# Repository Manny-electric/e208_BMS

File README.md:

# e208_BMS

This PCB can be used as a BMS for battery modules using the MAX17823BG BMS chip.
Modules that use this chip can be found in PSA cars like:
* Corsa-E
* Peugoet e-208 

This designe is based on work by bexander on the Openinverter Forum
https://openinverter.org/forum/viewtopic.php?t=1179&sid=5e96214b2f58e9805228647a1629a734

The PCB can be mounted in a Cinch encluosere 
* 581-01-30-065 main enclosure
* 581-01-18-038 Front / connector
* 581-01-18-023 Plug
* 425-00-00-872 pins

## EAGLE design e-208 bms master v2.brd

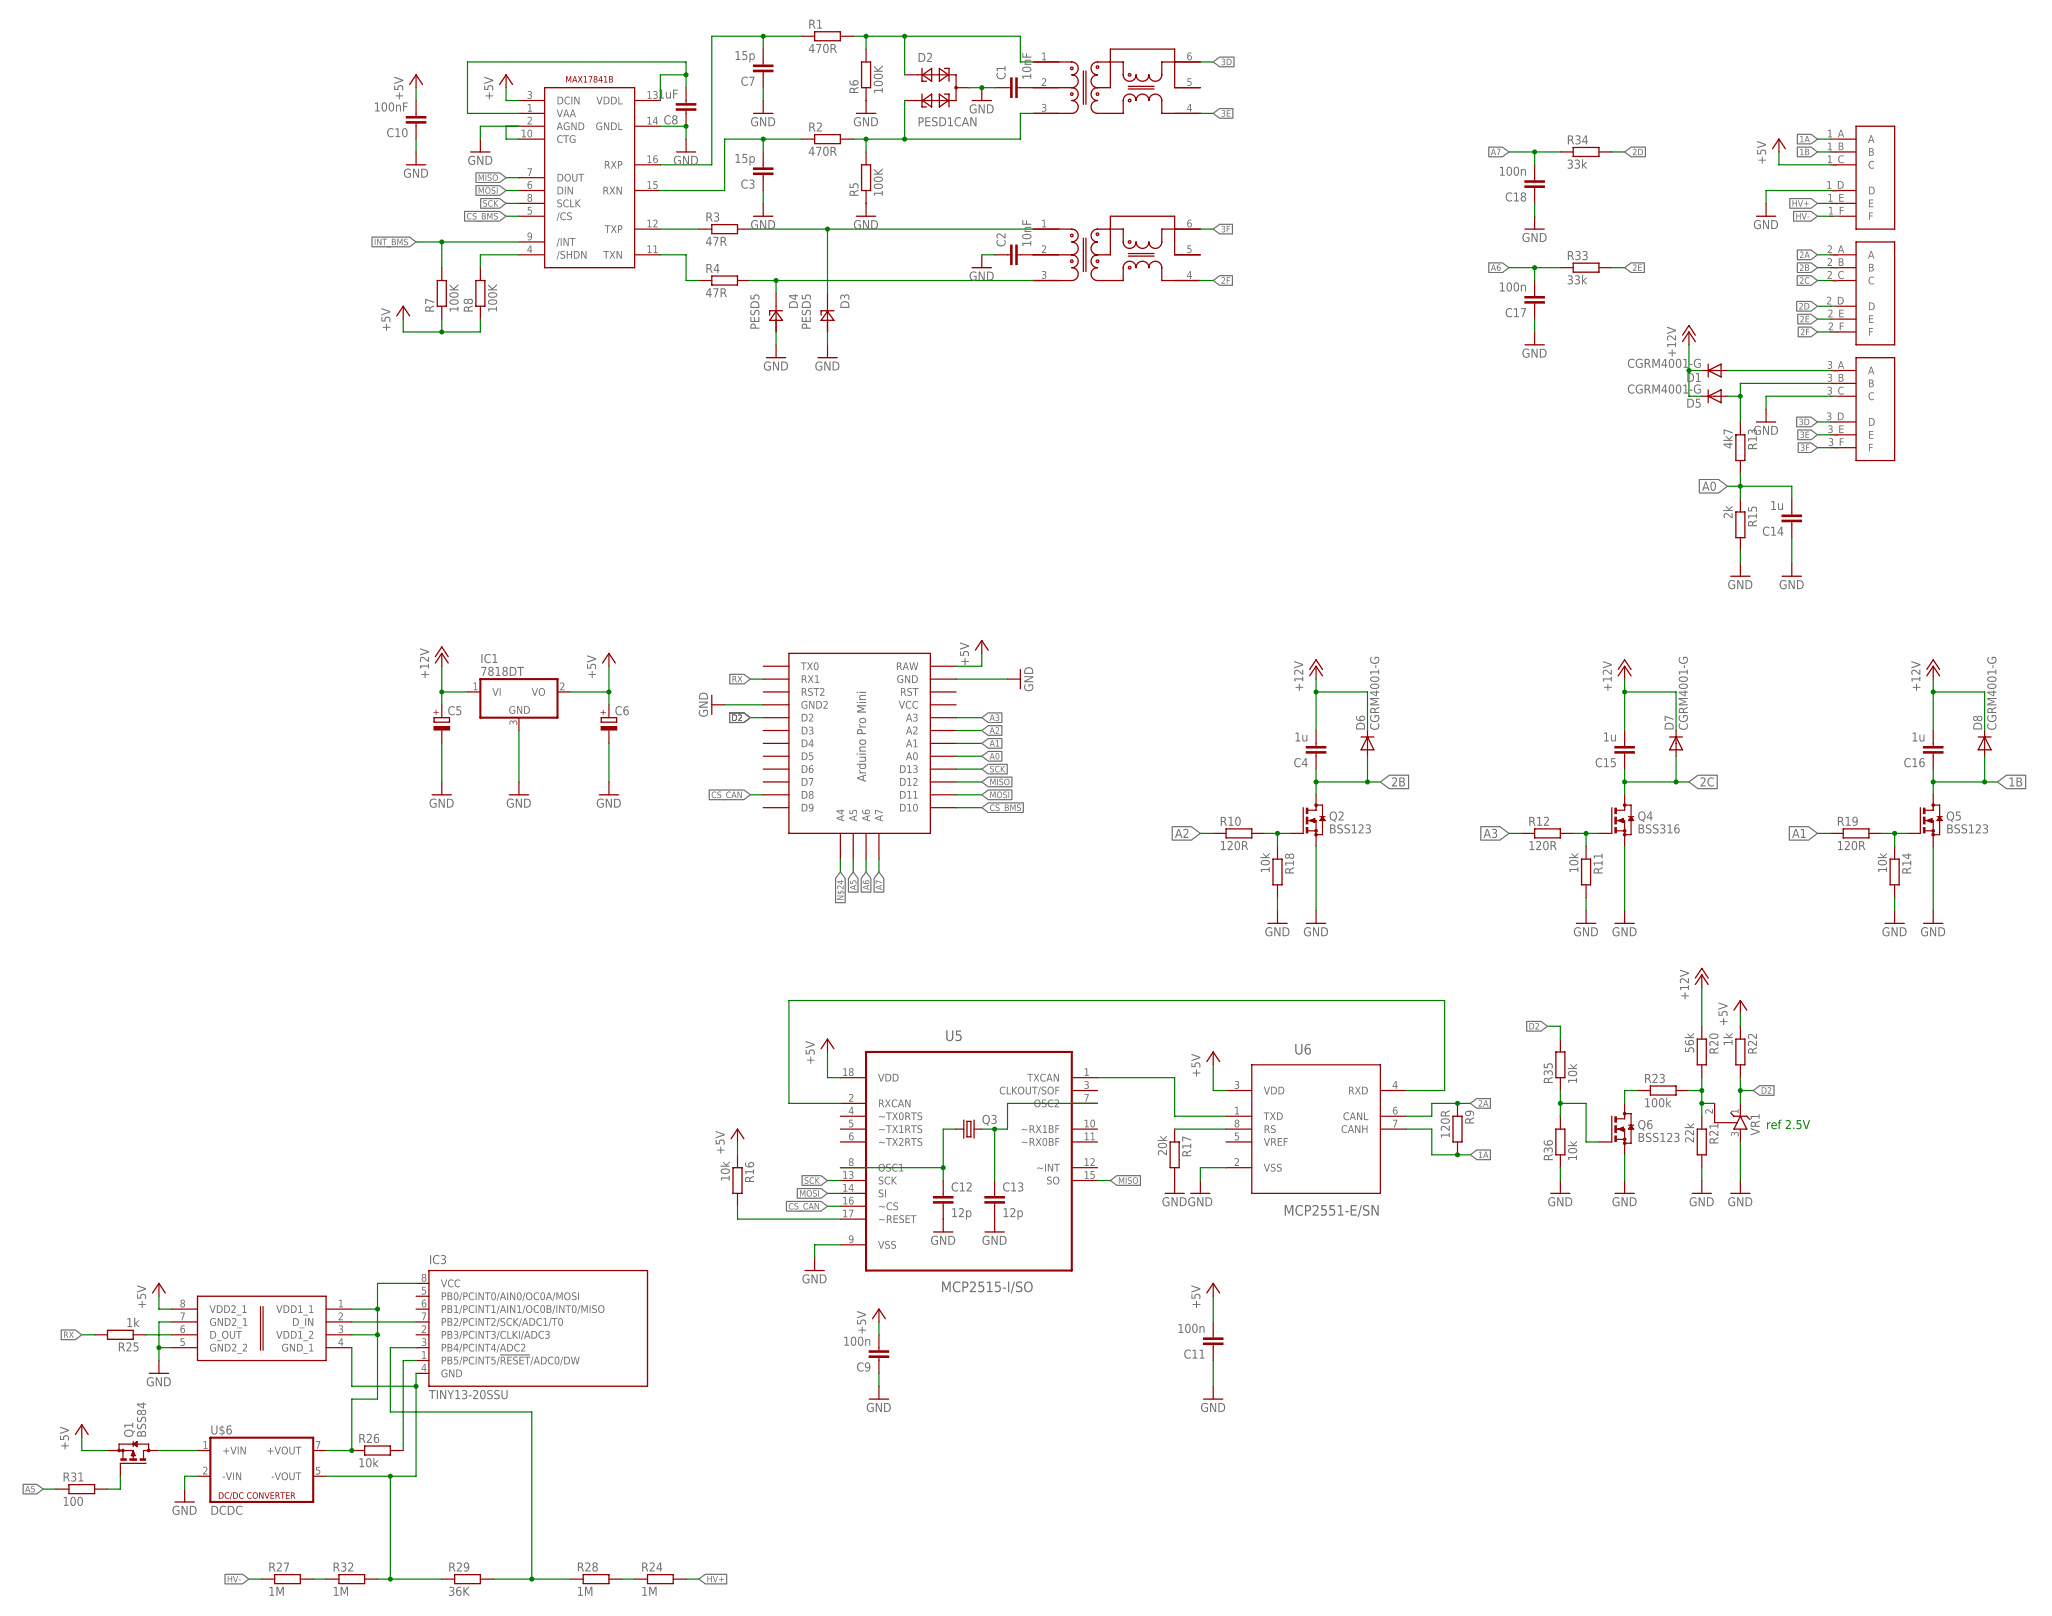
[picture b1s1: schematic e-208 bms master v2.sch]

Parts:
C1, C2: 10nF; C0805
C3, C7: 15p; C0805
C4, C14, C15, C16: 1u; C0805
C5, C6: CPOL-EU153CLV-1010; 153CLV-1010
C8: 1uF; C0805
C9, C11, C17, C18: 100n; C0805
C10: 100nF; C0805
C12, C13: 12p; C0603
D1, D5, D6, D7, D8: CGRM4001-G; SOD-123_MINI-SMA
D2: PESD1CAN; SOT23
D3, D4: PESD5; SOD323
IC1: 7818DT; TO252
IC3: TINY13-20SSU; 8S1
Q1: BSS84; SOT23
Q2, Q5, Q6: BSS123; SOT23
Q3: CRYSTALHC49U-V; HC49U-V
Q4: BSS316; SOT23
R1, R2: 470R; R0805
R3, R4: 47R; R0805
R5, R6, R7, R8: 100K; R0805
R9, R10, R12, R19: 120R; R0805
R11, R14, R16, R18, R26, R35, R36: 10k; R0805
R13: 4k7; R0805
R15: 2k; R0805
R17: 20k; R0805
R20: 56k; R0805
R21: 22k; R0805
R22, R25: 1k; R0805
R23: 100k; R0805
R24, R27, R28, R32: 1M; R0805
R29: 36K; R0805
R31: 100; R0805
R33, R34: 33k; R0805
U2: MAX17841B; TSSOP16
U5: MCP2515-I/SO; SOIC127P1034X264-18N
U6: MCP2551-E/SN; SOIC127P600X175-8N
U$1: 18P_ME
U$2: PRO-MINI-3
U$3, U$4: SM91502ALE
U$5: ADUM110N; SOIC8
U$6: DCDC
VR1: TL431CLPSOT23; SOT23

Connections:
1A: R9.2, U6.7 (CANH), U$1.1_A (A)
1B: C16.1, D8.A, Q5.3 (D), U$1.1_B (B)
2A: R9.1, U6.6 (CANL), U$1.2_A (A)
2B: C4.1, D6.A, Q2.3 (D), U$1.2_B (B)
2C: C15.1, D7.A, Q4.3 (D), U$1.2_C (C)
2D: R34.2, U$1.2_D (D)
2E: R33.2, U$1.2_E (E)
2F: U$1.2_F (F), U$4.4
3D: U$1.3_D (D), U$3.6
3E: U$1.3_E (E), U$3.4
3F: U$1.3_F (F), U$4.6
+5V: C6.+, C9.2, C10.2, C11.2, IC1.2 (VO), Q1.2 (S), R7.1, R8.1, R16.1, R22.1, U2.3 (DCIN), U5.18 (VDD), U6.3 (VDD), U$1.1_C (C), U$2.RAW, U$5.8 (VDD2_1)
+12V: C4.2, C5.+, C15.2, C16.2, D1.C, D5.C, D6.C, D7.C, D8.C, IC1.1 (VI), R20.1
A0: C14.2, R13.2, R15.1, U$2.A0
A1: R19.1, U$2.A1
A2: R10.1, U$2.A2
A3: R12.1, U$2.A3
A5: R31.1, U$2.A5
A6: C17.2, R33.1, U$2.A6
A7: C18.2, R34.1, U$2.A7
CS_BMS: U2.5 (/CS), U$2.D10
CS_CAN: U5.16 (~CS), U$2.D8
D2: R22.2, R35.2, U$2.D2, VR1.1 (C)
GND: C1.1, C2.1, C3.1, C5.-, C6.-, C7.1, C8.1, C9.1, C10.1, C11.1, C12.2, C13.2, C14.1, C17.1, C18.1, D2.3, D3.2, D4.2, IC1.3 (GND), Q2.2 (S), Q4.2 (S), Q5.2 (S), Q6.2 (S), R5.1, R6.1, R11.2, R14.2, R15.2, R17.2, R18.2, R21.2, R36.1, U2.2 (AGND), U2.10 (CTG), U2.14 (GNDL), U5.9 (VSS), U6.2 (VSS), U$1.1_D (D), U$1.3_C (C), U$2.GND, U$2.GND1 (GND2), U$5.5 (GND2_2), U$5.7 (GND2_1), U$6.2 (-VIN), VR1.3 (A)
HV+: R24.2, U$1.1_E (E)
HV-: R27.1, U$1.1_F (F)
INT_BMS: R7.2, U2.9 (/INT)
MISO: U2.7 (DOUT), U5.15 (SO), U$2.D12
MOSI: U2.6 (DIN), U5.14 (SI), U$2.D11
unnamed: D4.1, R4.2, U$4.3
unnamed: Q2.1 (G), R10.2, R18.1
unnamed: R20.2, R21.1, R23.2, VR1.2 (R)
unnamed: D3.1, R3.2, U$4.1
unnamed: Q6.3 (D), R23.1
unnamed: D1.A, U$1.3_A (A)
unnamed: C2.2, U$4.2
unnamed: C1.2, U$3.2
unnamed: R4.1, U2.11 (TXN)
unnamed: IC3.4 (GND), R29.1, R32.2, U$5.4 (GND_1), U$6.5 (-VOUT)
unnamed: Q4.1 (G), R11.1, R12.2
unnamed: R3.1, U2.12 (TXP)
unnamed: Q5.1 (G), R14.1, R19.2
unnamed: C3.2, R2.1, U2.15 (RXN)
unnamed: C7.2, R1.1, U2.16 (RXP)
unnamed: D2.1, R1.2, R6.2, U$3.1
unnamed: D2.2, R2.2, R5.2, U$3.3
unnamed: R8.2, U2.4 (/SHDN)
unnamed: C8.2, U2.1 (VAA), U2.13 (VDDL)
unnamed: U5.1 (TXCAN), U6.1 (TXD)
unnamed: U5.2 (RXCAN), U6.4 (RXD)
unnamed: C12.1, Q3.1, U5.8 (OSC1)
unnamed: C13.1, Q3.2, U5.7 (OSC2)
unnamed: D5.A, R13.1, U$1.3_B (B)
unnamed: R16.2, U5.17 (~RESET)
unnamed: R17.1, U6.8 (RS)
unnamed: Q6.1 (G), R35.1, R36.2
unnamed: Q1.3 (D), U$6.1 (+VIN)
unnamed: IC3.7 (PB2/PCINT2/SCK/ADC1/T0), U$5.2 (D_IN)
unnamed: R27.2, R32.1
unnamed: R24.1, R28.2
unnamed: R25.1, U$5.6 (D_OUT)
unnamed: IC3.1 (PB5/PCINT5/!RESET!/ADC0/DW), R26.2
unnamed: IC3.8 (VCC), R26.1, U$5.1 (VDD1_1), U$5.3 (VDD1_2), U$6.7 (+VOUT)
unnamed: Q1.1 (G), R31.2
unnamed: IC3.3 (PB4/PCINT4/ADC2), R28.1, R29.2
RX: R25.2, U$2.RX1
SCK: U2.8 (SCLK), U5.13 (SCK), U$2.D13

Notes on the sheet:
ref 2.5V

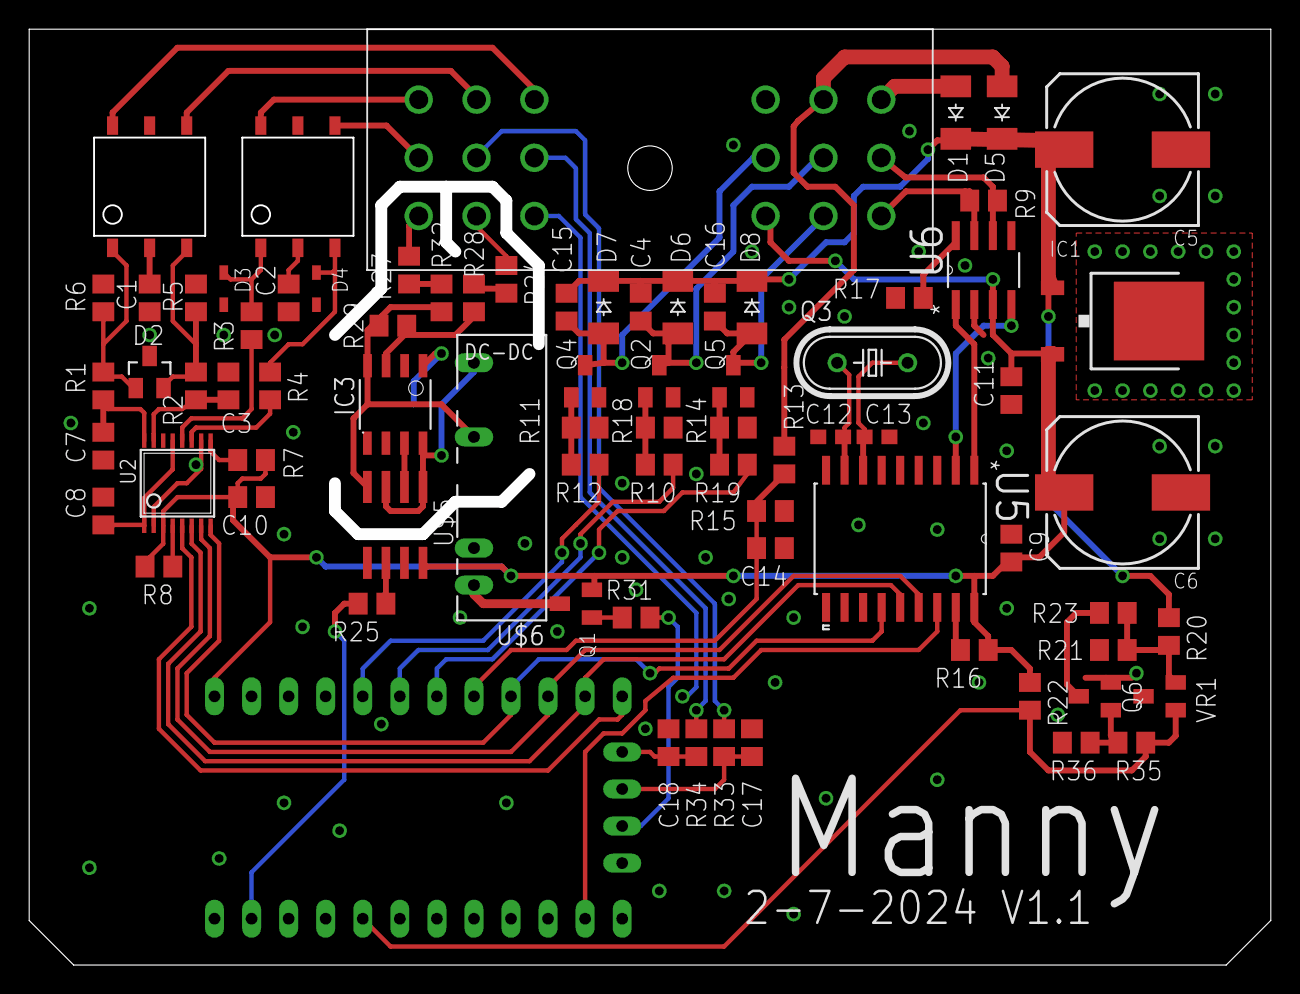
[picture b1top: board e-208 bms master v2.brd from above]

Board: 2 copper layers, 84.3 x 63.3 mm, 79 parts (1 on the bottom side), 67 nets.
